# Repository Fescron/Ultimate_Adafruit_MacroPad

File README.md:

# Ultimate_Adafruit_MacroPad

This repository contains **necessary components** and **fabrication instructions** for my **Ultimate Adafruit Macropad**, as well as the **code and macro-definitions** I run on it. **Configuration and usage instructions** are also listed here.

I've basically added two [NeoKey 1x4 boards](https://www.adafruit.com/product/4980) next to the [Adafruit Macropad](https://www.adafruit.com/product/5128) to simplify macro-layer-switching. I've found that pressing a button to change a macro-layer on the Macropad is much faster than rotating the encoder, certainly if there are (currently) more than 25 layers defined. The encoder is repurposed to change macro-selection-layers on the NeoKey buttons. To have an additional (apart from the button color) indication of what Macropad layer can be activated using a specific NeoKey button, I've also added a [1.3" 128x64 OLED display](https://www.adafruit.com/product/938) above the NeyKey boards.

I've subsequently (heavily) modified the original [Macropad Hotkeys code](https://learn.adafruit.com/macropad-hotkeys?view=all) to work with these additional buttons and display, as wel as added functionality to use other keyboard layouts (using code from [this](https://github.com/Neradoc/Circuitpython_Keyboard_Layouts) repository) and to dim the displays and button-LEDs after some time (using code from [this](https://github.com/M-Eldin/Adafruit-MacroPad-RP2040-Sleep) repository). Since the default firmware on the Macropad doesn't support two displays I've also had to compile new CircuitPython firmware to flash to the Macropad.

<br>

## 0 - Repository Structure

| Folder | Contents |
|---|---|
| [`CIRCUITPY`](CIRCUITPY/) | All files *as-is* on my Ultimate Adafruit Macropad. It contains libraries (`lib`), macros (`macros`), the main `code.py`-file, a quick reference to keycodes (`Keycodes.txt`) and a [VSCode](https://code.visualstudio.com/) workspace (`workspace.code-workspace`) to quickly open some files to I can edit them. |
| [`img`](img/) | Images displayed on this README. |
| [`pcb`](pcb/) | Two (custom) [KiCad](https://www.kicad.org/) PCBs to assemble the Ultimate Adafruit Macropad. |
| [`uf2`](uf2/) | A [CircuitPython](https://circuitpython.org/) firmware-file for the Adafruit Macropad with support for two screens. |

<br>

## 1 - Construction (Hardware)

### 1.1 - Materials

The **Ultimate Adafruit Macropad** is constructed using the materials from the tables below. Note that my version is *very fancy*, with very expensive (but amazing looking) windowed keycaps. These are certainly not required, and instead an [Adafruit MacroPad RP2040 Starter Kit](https://www.adafruit.com/product/5128) with included basic keycaps and switches can also be purchased.

Also note that the NeoKey 1x4 boards ship without switches and keycaps, they need to be purchased separately. In case the [Adafruit MacroPad RP2040 Starter Kit](https://www.adafruit.com/product/5128) is bought (instead of the [Adafruit MACROPAD RP2040 Bare Bones](https://www.adafruit.com/product/5100) board) individual switches and keycaps still need to be purchased for the NeoKey boards.

| Qty | Description | Link |
|---|---|---|
| 1 | Adafruit MACROPAD RP2040 Bare Bones | https://www.adafruit.com/product/5100 |
| 2 | Kailh Mechanical Key Switches - Tactile Brown - 10 pack | https://www.adafruit.com/product/4954 |
| 2 | NeoKey 1x4 QT I2C | https://www.adafruit.com/product/4980 |
| 20 | Black Windowed Lamp R4 Keycap for MX Compatible Switches | https://www.adafruit.com/product/5112 |
| 1 | STEMMA QT / Qwiic JST SH 4-Pin Cable - 50mm Long | https://www.adafruit.com/product/4399 |
| 1 | Monochrome 1.3" 128x64 OLED graphic display - STEMMA QT / Qwiic | https://www.adafruit.com/product/938 |
| 1 | Anodized Aluminum Machined Knob - Black - 20mm Diameter | https://www.adafruit.com/product/5527 |
| 1 | Adafruit MacroPad RP2040 Enclosure + Hardware Add-on Pack | https://www.adafruit.com/product/5103 |
| 1 | Baseboard PCB | (see [these](pcb/ultimate-adafruit-macropad-baseboard/gerber/) gerber-files) |
| 1 | Keyplate PCB | (see [these](pcb/ultimate-adafruit-macropad-keyplate/gerber/) gerber-files) |

Additionally some more generic items are necessary and/or can be useful.

| Description | Usage | Link(s) |
|---|---|---|
| Male (and female) 2.54mm/0.1" pinheaders | Mounting the NeoKey and OLED boards to the Baseboard PCB | https://www.adafruit.com/product/392 https://www.adafruit.com/product/598 |
| Black Nylon Machine Screw and Stand-off Set - M2.5 Thread | Mounting the NeoKey and OLED boards to the Baseboard PCB | https://www.adafruit.com/product/3299 |
| Black Nylon Machine Screw and Stand-off Set - M3 Thread | Mounting the Macropad to the Boaseboard PCB | https://www.adafruit.com/product/4685 |
| 2 pcs Laptop riser feet | Setting the board on an angle for easier usage | https://www.aliexpress.com/item/1005003557570061.html |
| 12x5mm 40 pcs round rubber pads | Making sure the board doesn't slide around | https://www.aliexpress.com/item/33030992785.html |
| Carrying case | Protecting the board during travel | https://www.aliexpress.com/item/1005001855670902.html |

<br>

### 1.2 - Assembly

As the last two entries in the first material-table already suggested, I've also designed two custom PCBs to facilitate a fairly easy assembly and final sturdy device. The [Baseboard PCB](pcb/ultimate-adafruit-macropad-baseboard/) is used to mount all boards to a single PCB, while also facilitating some interconnections between the components. Only a single Stemma QT / Qwiic cable (in an out-of-sight spot) is required, the rest of the connections are done by the Baseboard.

The second PCB, the [Keyplace PCB](pcb/ultimate-adafruit-macropad-keyplate/), is used to secure the eight mechanical switches to the two NeoKey boards. It basically has the same functionality as the keyplace-PCB does for the Adafruit Macropad (included in the [Adafruit MacroPad RP2040 Enclosure + Hardware Add-on Pack](https://www.adafruit.com/product/5103) or [Adafruit MacroPad RP2040 Starter Kit](https://www.adafruit.com/product/5128)).

#### The assembly-steps are the following

1. Solder male 2.54mm/0.1" pinheaders to the Baseboard (one with 01x08 pins for the OLED, two with 01x06 pins for the NeoKey boards).
2. Close solder-jumper `A0` of the left-most NeoKey 1x4 board to set its I2C address to `0x31`. The right-most NeoKey 1x4 board will keep its default address of `0x30`.
3. Solder female 01x06 2.54mm/0.1" headers to the NeoKey boards.
4. Solder a female 01x08 2.54mm/0.1" header to the OLED display. Also cut the mounting-holes on the bottom of this board so it can be mounted closer to the NeoKey boards.
5. Screw the Macropad to the Baseboard using M3 hardware.
6. Screw the NeoKey boards to the Baseboard using M2.5 hardware.
7. Connect the STEMMA QT / Qwiic cable from the Macropad to the top of the left-most NeoKey board.
8. Screw the OLED display to the Baseboard using M2.5 hardware.
9. Mount the mechanical keys to the Macropad. Make sure to not forget the keyplate in between the Macropad and the keys.
10. Mount the mechanical keys to the NeoKey boards. Make sure to not forget the (custom) keyplate in between the boards and the keys.
11. Mount the rotary encoder knob on the rotary encoder. Put the keycaps on the mechanical switches. Mount the riser feet to the bottom of the Baseboard.
12. (Optional, if the carrying case is used): Cut a foam-insert for the inside of the case to keep the Ultimate Adafruit Macropad from moving around.

|  |  |
|--|--|

<br>

## 2 - Firm/Software

### 2.1 - Firmware

As already mentioned, the default [CircuitPython](https://circuitpython.org/) firmware for the Adafruit Macropad doesn't support two screens. Fortunately it is possible to build `.uf2`-files yourself which do support this. The result of this is placed in the [`uf2`](uf2/) directory on this repository.

<details>

  <summary>For reference, the following (Linux/Ubuntu) steps/commands can be used to build the file yourself</summary>
  
  ```bash
  ## https://learn.adafruit.com/building-circuitpython/linux
  # Install additional software
  sudo apt install build-essential
  sudo add-apt-repository ppa:git-core/ppa
  sudo add-apt-repository ppa:pybricks/ppa
  # Download the appropriate ARM Cortex-M toolchain
  # (for CircuitpPython 8.x: 10-2020-q4-major https://developer.arm.com/downloads/-/gnu-rm)
  # Unpack it in a convenient directory
  mkdir ~/bin
  cd ~/bin
  tar xvf gcc-arm-none-eabi-10-2020-q4-major-x86_64-linux.tar.bz2
  # Add a link to the toolchain executables in PATH
  sudo nano ~/.profile
    export PATH=/home/$USER/bin/gcc-arm-none-eabi-10-2020-q4-major/bin:$PATH
  # Logout and log back in
  # Check if the link is correctly configured
  which arm-none-eabi-gcc

  ## https://learn.adafruit.com/building-circuitpython/build-circuitpython
  # Clone the repository
  git clone https://github.com/adafruit/circuitpython.git
  cd circuitpython
  # Install needed Python packages from pypi.org.
  pip3 install --upgrade -r requirements-dev.txt
  pip3 install --upgrade -r requirements-doc.txt
  # Checkout the latest stable branch (as per https://circuitpython.org/board/adafruit_macropad_rp2040/)
  git checkout 8.2.8
  # Fetch submodules (for a specific ports/... device)
  cd ports/raspberrypi
  make fetch-port-submodules
  # Build mpy-cross
  cd ../..
  make -C mpy-cross

  ## https://todbot.com/blog/2022/05/19/multiple-displays-in-circuitpython-compiling-custom-circuitpython/
  # Build for the Adafruit Macropad, with the display limit set to "2"
  cd ports/raspberrypi
  echo "#define CIRCUITPY_DISPLAY_LIMIT (2)" >> boards/adafruit_macropad_rp2040/mpconfigboard.h
  make -j12 BOARD=adafruit_macropad_rp2040
  ```

</details>

#### The firmware flashing steps are the following

1. Make sure the board is plugged-in to a computer
2. Quickly double-press the <kbd>reset</kbd> button on the Macropad to put it in the "firmware flashing" mode.
   1. If correctly activated a `RPI-RP2` drive shows up on the computer.
   2. If this doesn't work, use the following sequence to activate this mode.
      1. Hold down the encoder push-button
      2. Press the <kbd>reset</kbd> button
      3. Release the encoder push-button
3. Copy the `.uf2`-file to the `RPI-RP2` drive
4. Wait some time for the flashing to be complete

<br>

### 2.2 - Libraries (and other files)

After the firmware has been updated, the necessary libraries (and other files) need to be copied to the (Ultimate) Adafruit Macropad. One can simply copy all contents inside the [`CIRCUITPY`](CIRCUITPY/) directory of this repository to the Macropad.

<br>

### 2.3 - Software Configuration

#### 2.3.1 - Main Code

If all of the necessary files are copied to the Macropad, the customization can begin. [`CIRCUITPY/code.py`](CIRCUITPY/code.py) is the main configuration file. The macro-definitions can be found in [`CIRCUITPY/macros`](CIRCUITPY/macros). All of the files start with a number so they are sorted in a specific order. The number is also used to configure the NeoKey layers (`NEOKEY_BUTTONS`).

Inside [`CIRCUITPY/code.py`](CIRCUITPY/code.py) are a few configuration-variables to change some functionality.

- `KEYBOARD_LAYOUT`
  - `KEYBOARD_LAYOUT = 0`: Select <kbd>US QWERTY</kbd> as keyboard layout.
  - `KEYBOARD_LAYOUT = 1`: Select <kbd>Belgian AZERTY</kbd> as keyboard layout (*default*).
  - `KEYBOARD_LAYOUT = 2`: Select my <kbd>Custom Belgian AZERTY</kbd> keyboard layout where the numbers and characters on the number-row are swapped around.
- `MACRO_FOLDER`
  - `MACRO_FOLDER = '/macros'`: Select the folder where the code looks for macro-definitions.
- `NEOKEY_BUTTONS_START_LAYER`: Select the start-up NeoKey button-layer.
- `NEOKEY_BUTTONS_START_BUTTON`: Select the start-up NeoKey button.
- `NEOKEY_BUTTONS`
  - This is the NeoKey layer-definition. Layers can be changed by turning the rotary encoder on the Macropad.
  - The definition-syntax is loosely based on those of the the macro-definitions. The structure is the following (below is an example of a layer-definition).
    - A layer always needs a title-text (although it can be a zero-length string). The title is displayed on the first line of the OLED display above the NeoKey buttons.
    - The button-row definitions very closely resemble the functionality of the Macropad macro-definitions. The necessary fields are the following.
      1. A hexadecimal color-code to light-up the NeoKey button in case the page is not activated. If the layer is selected (after a button-press on the NeoKey) the key itself lights up white.
      2. A (short) text explaining the functionality present on the layer(s) which can be activated with this button. The text is also displayed in the corresponding button-location on the OLED display above the NeoKeys. The text on the screen of an activated layer also gets inverted.
      3. A list of numbers corresponding to the Macropad layers which can be activated (or cycled) after pressing a specific NeoKey button. The numbers are the same starting-numbers from the files in [`CIRCUITPY/macros`](CIRCUITPY/macros).
         - In case no macros need to be bound to a NeoKey button, make sure to still enter a (placeholder) file-number in this list. An "unused" button should have the following syntax: `(0x000000, "", [0]),`
- `TIMEOUT_S`
  - `TIMEOUT_S = 10 * 60`: Set the timeout to 10 minutes, after which the OLED displays and button-LEDs will dim. All button-functionality however still remains active.

```python
NEOKEY_BUTTONS = [
  [
    # Layer title
    "Base [1/3] AltiumSch",
    # Button definitions
    [
        # First row
        (0x004000, "AltCode1,2", [0, 1]),   # Alt-codes 1 & 2
        (0x404000, "Base,Queri", [3, 24]),  # Altium Schematic 1 & Validation Queries
        # Second row
        (0x000040, "Word1,4",    [2, 16]),  # Word 1 & 4
        (0x404000, "Hierarch",   [4]),      # Altium Schematic 2
        # Third row
        (0x000040, "Word2,3",    [20, 23]), # Word 2 & 3
        (0x404000, "Varia,Algn", [5, 22]),  # Altium Schematic 3 & Alignment
        # Fourth row
        (0x004040, "Outl,Excl",  [18, 26]), # Outlook & Excel
        (0x404000, "Col,NetCol", [15, 11])  # Altium Colors & Net-colors
    ]
  ],
]
```

<br>

#### 2.3.2 - Macropad layer-definitions

The build-up of the macro-file definitions ([`CIRCUITPY/macros`](CIRCUITPY/macros)) is unchanged compared to those of a "regular" Adafruit Macropad, and thus can perfectly be used in a "barebones" setup. Because of this the syntax won't be explicitly explained here, only some "tricks" I used when defining my macro-files.

- When there is a ``` ` ```-character at the **front** of a macro-label on the OLED display, it means a right-click mouse-action is used.
- When there is a ``` ` ```-character at the **end** of a macro-label on the OLED display, it means some sort of custom keyboard-shortcut was used. Or, in the case of the Altium *color*-pages, a non-standard color was defined.

<br>

## 3 - Usage

With the **Ultimate Adafruit Macropad** macro-definition-pages can be switched to by simply pressing one of the NeoKey buttons on the left of the Macropad, instead of rotating the encoder. The OLED display above the NeoKey buttons is used to show informating regarding these Macropad layers. The LED of the last selected (group of) page(s) lights up bright white, and the text on the OLED is inverted. The other NeoKey LEDs light up according to their defined color in `NEOKEY_BUTTONS` in the [`CIRCUITPY/code.py`](CIRCUITPY/code.py) file.

The latter file is used to do the main configuration, such as defining which Macropad layers (placed in [`CIRCUITPY/macros`](CIRCUITPY/macros)) can be activated using which NeoKey buttons. When there are multiple macro-definition-pages linked to a single NeoKey button (more than one number in the square brackets in `NEOKEY_BUTTONS`), subsequent presses on the same key rotate between all pages defined in the list. The last selected page is remembered in case another NeoKey button is pressed to select another (group of) page(s), or a whole NeoKey layer is changed using the rotary encoder. The first line on the OLED display above the NeoKey buttons also shows a title of the current layer, which is also configured in [`CIRCUITPY/code.py`](CIRCUITPY/code.py).

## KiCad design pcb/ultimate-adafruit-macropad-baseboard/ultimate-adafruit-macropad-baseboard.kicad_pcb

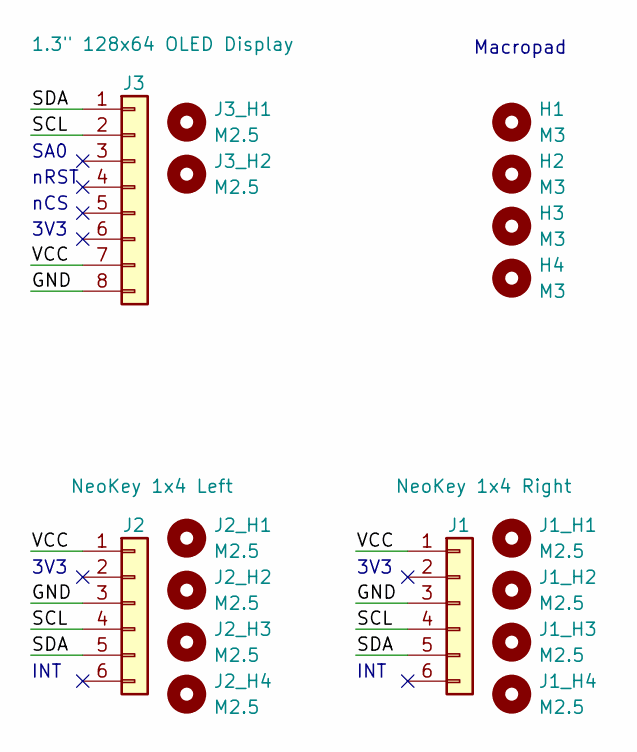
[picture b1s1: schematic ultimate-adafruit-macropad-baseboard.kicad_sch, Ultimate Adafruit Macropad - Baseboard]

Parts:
H1, H2, H3, H4: MountingHole; MountingHole_3.2mm_M3
J1, J2: Conn_01x06; PinSocket_1x06_P2.54mm_Vertical
J1_H1, J1_H2, J1_H3, J1_H4, J2_H1, J2_H2, J2_H3, J2_H4, J3_H1, J3_H2: MountingHole; MountingHole_2.7mm_M2.5
J3: Conn_01x08; PinSocket_1x08_P2.54mm_Vertical

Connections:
/GND: J1.3, J2.3, J3.8
/SCL: J1.4, J2.4, J3.2
/SDA: J1.5, J2.5, J3.1
/VCC: J1.1, J2.1, J3.7

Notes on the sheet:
3V3
nCS
Macropad
INT
SA0
nRST

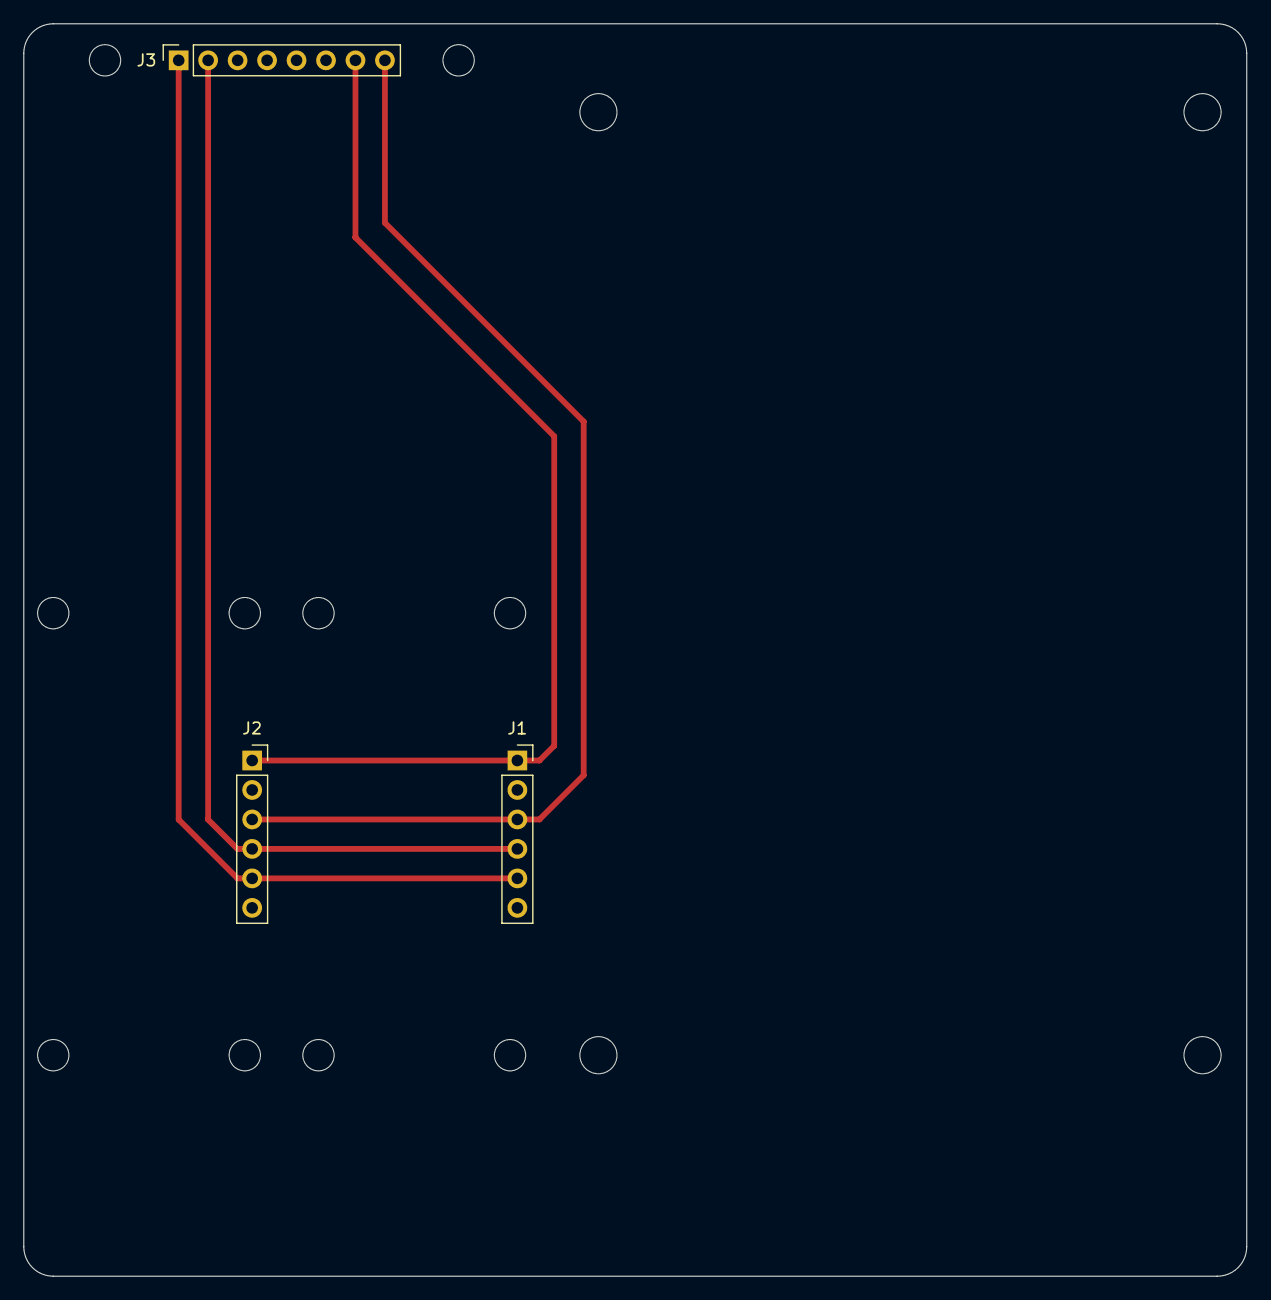
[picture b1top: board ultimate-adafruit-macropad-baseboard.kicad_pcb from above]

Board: 2 copper layers, 105.4 x 107.9 mm, 17 parts (0 on the bottom side), 4 nets.

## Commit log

2023-02-04 Added all initial files
2023-02-04 Updated some texts
2023-02-04 Fixed date
2023-02-04 Switched to QWERTY by default
2023-02-04 Added notes about the "`" usage in labels ## Added case link and picture
2023-02-14 Added picture of the back of the macropad ## Re-organized img in readme
2024-02-18 Reworked everything to v1.0
2024-02-18 Added OLED display to BOM
2024-02-18 Fixed badge

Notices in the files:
README.md:
License: MIT
